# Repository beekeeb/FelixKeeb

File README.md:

# FelixKeeb

The FelixKeeb is an open source 5×12+4 (5×6+2 on each side) split ortholinear keyboard with hotswap sockets support released by [beekeeb](https://beekeeb.shop). It is based on Cipulot’s [helixhschoc](https://github.com/cipulot/helixhschoc) and MakotoKurauchi’s [helix](https://github.com/MakotoKurauchi/helix).

## Quick Links

* [Precompiled firmware](https://docs.beekeeb.com/felixkeeb#precompiled-firmware)
* [beekeeb showcase](https://showcase.beekeeb.com/felixkeeb/)

## Firmware

* [QMK](https://github.com/qmk/qmk_firmware) - compatible with helix/rev2
* [Vial](https://github.com/vial-kb/vial-qmk) (based on QMK) - supported
* [ZMK](https://github.com/zmkfirmware/zmk) - supported

Precompiled firmware can be found at https://docs.beekeeb.com/felixkeeb.

## Features

* Hotswap Sockets: Changing key switches whenever you want

### Wireless

* nice!view support
* Onboard JST battery sockets: no battery soldering required & easily swapping batteries
* Power (on/off) switches: saving power by turning off the keyboard when it is not in used

### Wired

* OLED display support
* USB-C connectors: No pin shorting problems caused by TRRS jacks
* Compatible with Helix/rev2 VIAL Firmware

## Case
* A basic case using with MX key switches is [available in Printables](https://www.printables.com/model/957449).

## License

Photos, logos, external symbols and footprints are not covered by the LICENSE in this repo.

External symbols and footprints:

* [foostan/kbd](http://github.com/foostan/kbd)
* [nice_view.pretty](https://github.com/petejohanson/crkbd/tree/board/corne-ultralight/corne-ultralight/pcb/nice_view.pretty) from petejohanson's [Corne Ultralight](https://github.com/petejohanson/crkbd/tree/board/corne-ultralight)

## Credits

This open source hardware project is created by [beekeeb](https://beekeeb.shop) and other contributors. It is based on Cipulot’s [helixhschoc](https://github.com/cipulot/helixhschoc) and MakotoKurauchi’s [helix](https://github.com/MakotoKurauchi/helix).

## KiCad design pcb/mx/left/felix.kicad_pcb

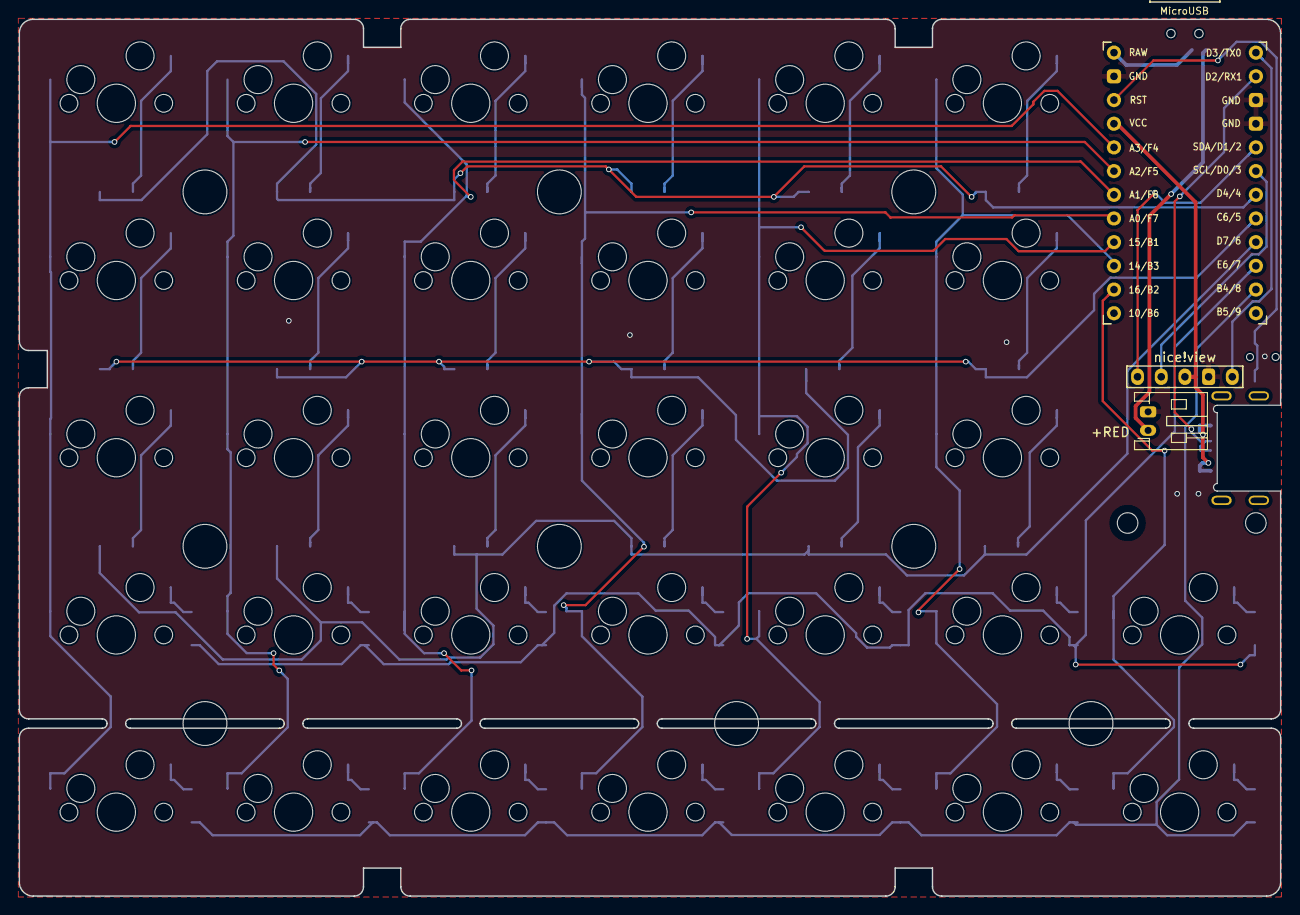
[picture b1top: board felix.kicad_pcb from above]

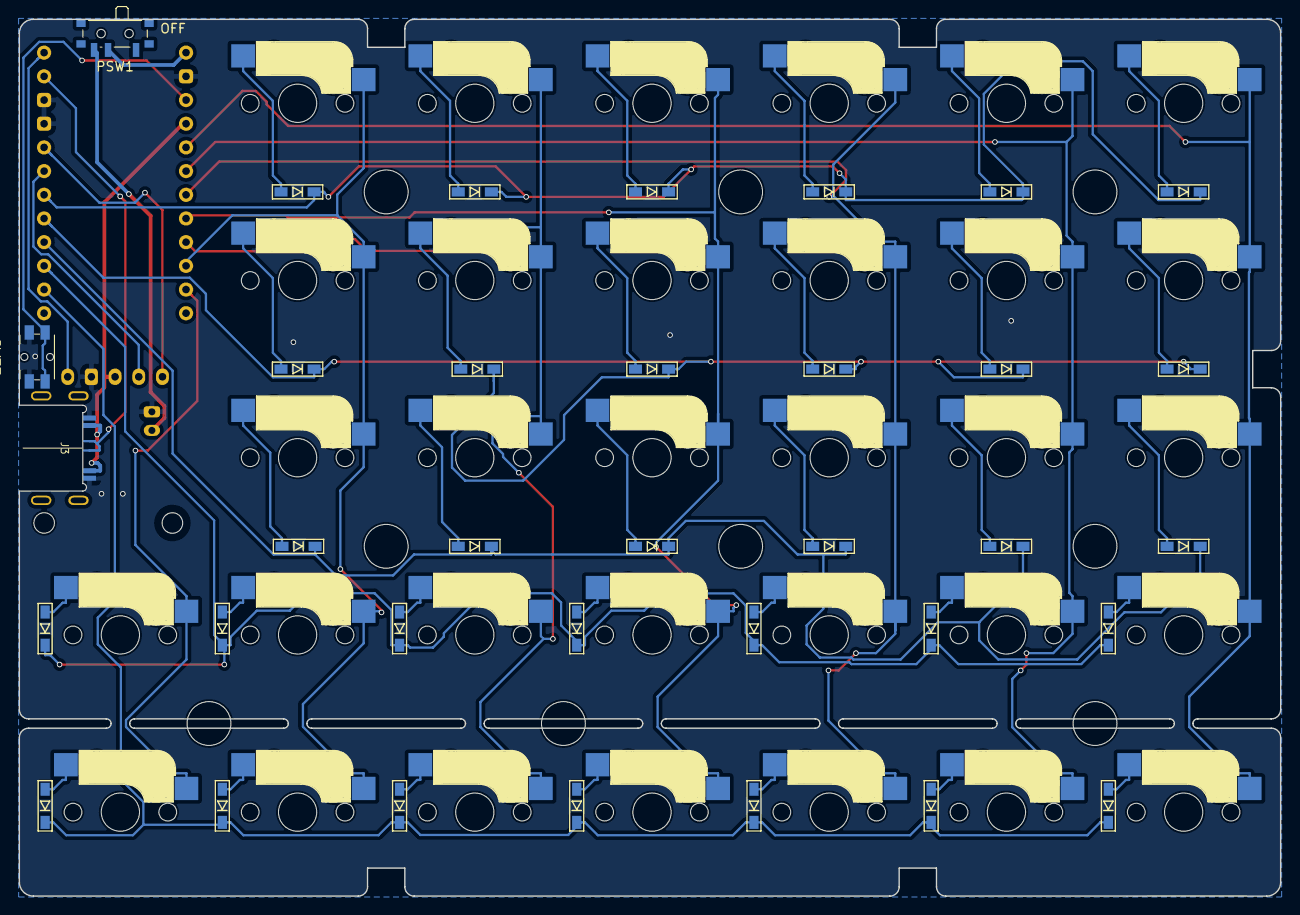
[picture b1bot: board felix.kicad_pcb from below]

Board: 2 copper layers, 135.2 x 94.0 mm, 81 parts (35 on the bottom side), 53 nets.

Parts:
BATJ1: Conn_01x02_Female; JST_PH_S2B-PH-K_1x02_P2.00mm_Horizontal
D1, D2, D3, D4, D5, D6, D7, D8, D9, D10, D11, D12, D13, D14, D15, D16, D17, D18, D19, D20, D21, D22, D23, D24, D25, D26, D27, D28, D29, D30, D31, D32: D; D3_SMD_v2
H1, H2, H3, H4, H5, H6, H7, H8, H9: MountingHole; HOLE_M2_TH
H10, H13: MountingHole; HOLE_M2
J2: OLED; nice_view_1side
J3: USB_C_Receptacle; TYPE-C-31-M-14-custom-summer
PSW1: SW_SPST; SW_SPDT_PCM12
SW1, SW2, SW3, SW4, SW5, SW6, SW7, SW8, SW9, SW10, SW11, SW12, SW13, SW14, SW15, SW16, SW17, SW18, SW19, SW20, SW21, SW22, SW23, SW24, SW25, SW26, SW27, SW28, SW29, SW30, SW31, SW32: SW_PUSH; CherryMX_Hotswap
SW33: Reset; Panasonic_EVQPUL_EVQPUC
U1: ProMicro; ProMicro_v3

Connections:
+BATT: PSW1.2 (B), U1.24 (RAW)
/~RESET: SW33.2, U1.22 (RESET)
CS: J2.5, U1.1 (TXO(PD3))
GND: BATJ1.2, J2.4, J3.A1 (GND), SW33.1, U1.3 (GND), U1.4 (GND), U1.23 (GND)
unnamed: BATJ1.1, PSW1.3 (C)
unnamed: D1.2 (A), SW1.2
unnamed: D2.2 (A), SW2.2
unnamed: D3.2 (A), SW3.2
unnamed: D4.2 (A), SW4.2
unnamed: D5.2 (A), SW5.2
unnamed: D6.2 (A), SW6.2
unnamed: D7.2 (A), SW7.2
unnamed: D8.2 (A), SW8.2
unnamed: D9.2 (A), SW9.2
unnamed: D10.2 (A), SW10.2
unnamed: D11.2 (A), SW11.2
unnamed: D12.2 (A), SW12.2
unnamed: D13.2 (A), SW13.2
unnamed: D14.2 (A), SW14.2
unnamed: D15.2 (A), SW15.2
unnamed: D16.2 (A), SW16.2
unnamed: D17.2 (A), SW17.2
unnamed: D18.2 (A), SW18.2
unnamed: D19.2 (A), SW19.2
unnamed: D20.2 (A), SW20.2
unnamed: D21.2 (A), SW21.2
unnamed: D22.2 (A), SW22.2
unnamed: D23.2 (A), SW23.2
unnamed: D24.2 (A), SW24.2
unnamed: D25.2 (A), SW25.2
unnamed: D26.2 (A), SW26.2
unnamed: D27.2 (A), SW27.2
unnamed: D28.2 (A), SW28.2
unnamed: D29.2 (A), SW29.2
unnamed: D30.2 (A), SW30.2
unnamed: D31.2 (A), SW31.2
unnamed: D32.2 (A), SW32.2
SCL: J2.2, U1.6 (D3(PD0))
SDA: J2.1, U1.5 (D2(PD1))
VCC: J2.3, J3.A4 (VBUS), U1.21 (VCC)
col0: SW1.1, SW7.1, SW13.1, SW19.1, SW26.1, U1.20 (A3(PF4))
col1: SW2.1, SW8.1, SW14.1, SW20.1, SW27.1, U1.19 (A2(PF5))
col2: SW3.1, SW9.1, SW15.1, SW21.1, SW28.1, U1.18 (A1(PF6))
col3: SW4.1, SW10.1, SW16.1, SW22.1, SW29.1, U1.17 (A0(PF7))
col4: SW5.1, SW11.1, SW17.1, SW23.1, SW30.1, U1.16 (SCK(PB1))
col5: SW6.1, SW12.1, SW18.1, SW24.1, SW31.1, U1.15 (MISO(PB3))
col6: SW25.1, SW32.1, U1.14 (MOSI(PB2))
data: J3.A7 (D-), J3.B7 (D-), U1.2 (RXI(PD2))
row0: D1.1 (K), D2.1 (K), D3.1 (K), D4.1 (K), D5.1 (K), D6.1 (K), U1.7 (D4(PD4))
row1: D7.1 (K), D8.1 (K), D9.1 (K), D10.1 (K), D11.1 (K), D12.1 (K), U1.8 (D5(PC6))
row2: D13.1 (K), D14.1 (K), D15.1 (K), D16.1 (K), D17.1 (K), D18.1 (K), U1.9 (D6(PD7))
row3: D19.1 (K), D20.1 (K), D21.1 (K), D22.1 (K), D23.1 (K), D24.1 (K), D25.1 (K), U1.10 (D7(PE6))
row4: D26.1 (K), D27.1 (K), D28.1 (K), D29.1 (K), D30.1 (K), D31.1 (K), D32.1 (K), U1.11 (D8(PB4))

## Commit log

2024-07-29 Add case info
